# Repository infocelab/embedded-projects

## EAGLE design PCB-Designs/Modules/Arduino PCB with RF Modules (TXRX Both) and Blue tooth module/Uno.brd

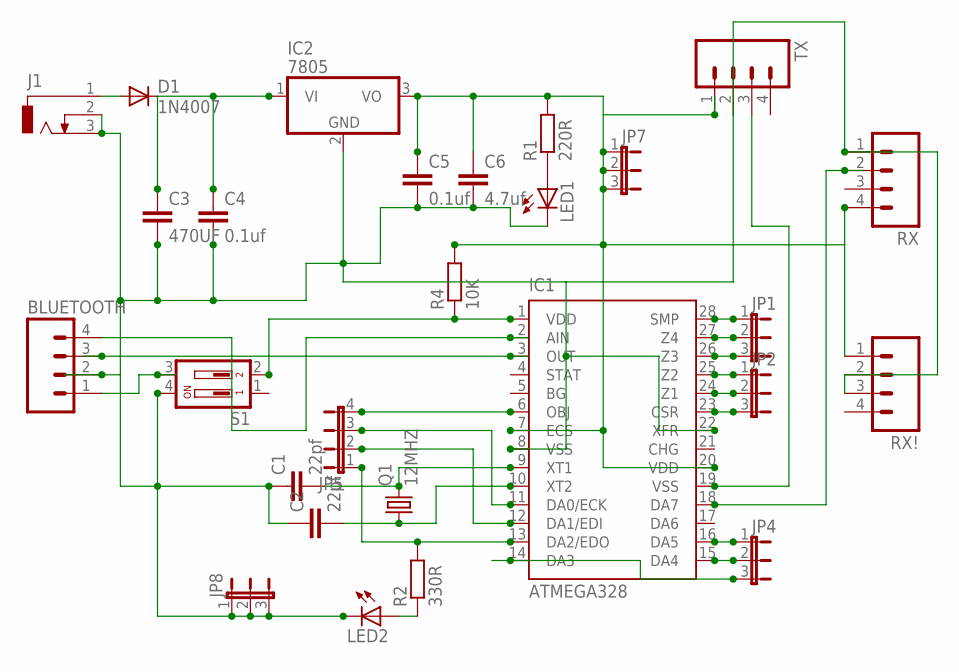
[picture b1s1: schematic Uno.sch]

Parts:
BLUETOOTH: M04; 04P
C1, C2: 22pf; C2.5-2
C3: 470UF; C2.5-2
C4, C5: 0.1uf; C2.5-2
C6: 4.7uf; C2.5-2
D1: 1N4007; DO41-10
IC1: ATMEGA328; DIL28-3
IC2: 7805; TO220V
J1: DCJ0303
JP1, JP2, JP4, JP7, JP8: JP2E; JP2
JP5: JP4E; JP4
LED1, LED2: LED3MM
Q1: 12MHZ; HC49/S
R1: 220R; 0207/10
R2: 330R; 0207/10
R4: 10K; 0207/10
RX: M04; 04P
RX!: M04; 04P
S1: DP02; DP-02
TX: M04; 04P

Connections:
unnamed: C1.2, IC1.9 (XT1), Q1.2
unnamed: C2.2, IC1.10 (XT2), Q1.1
unnamed: D1.A, J1.1
unnamed: C5.1, C6.1, IC1.7 (ECS), IC1.20 (VDD), IC2.3 (VO), JP7.1, JP7.2, JP7.3, R1.2, R4.2, RX.4, RX!.1, TX.1
unnamed: BLUETOOTH.2, C1.1, C2.1, C3.2, C4.2, C5.2, C6.2, IC1.8 (VSS), IC1.22 (XFR), IC2.2 (GND), J1.2, J1.3, JP8.1, JP8.2, JP8.3, LED1.K (C), LED2.K (C), RX.1, RX!.2, RX!.3, S1.4, TX.2
unnamed: LED1.A, R1.1
unnamed: C3.1, C4.1, D1.C, IC2.1 (VI)
unnamed: IC1.28 (SMP), JP1.1
unnamed: IC1.27 (Z4), JP1.2
unnamed: IC1.26 (Z3), JP1.3
unnamed: IC1.25 (Z2), JP2.1
unnamed: IC1.24 (Z1), JP2.2
unnamed: IC1.23 (CSR), JP2.3
unnamed: BLUETOOTH.4, IC1.2 (AIN)
unnamed: BLUETOOTH.1, S1.3
unnamed: BLUETOOTH.3, IC1.3 (OUT)
unnamed: IC1.6 (OBJ), JP5.4
unnamed: IC1.12 (DA1/EDI), JP5.2
unnamed: IC1.11 (DA0/ECK), JP5.3
unnamed: IC1.13 (DA2/EDO), JP5.1, R2.2
unnamed: IC1.14 (DA3), JP4.3
unnamed: IC1.15 (DA4), JP4.2
unnamed: IC1.16 (DA5), JP4.1
unnamed: IC1.18 (DA7), RX.2
unnamed: IC1.19 (VSS), TX.3
unnamed: IC1.1 (VDD), R4.1, S1.2
unnamed: LED2.A, R2.1

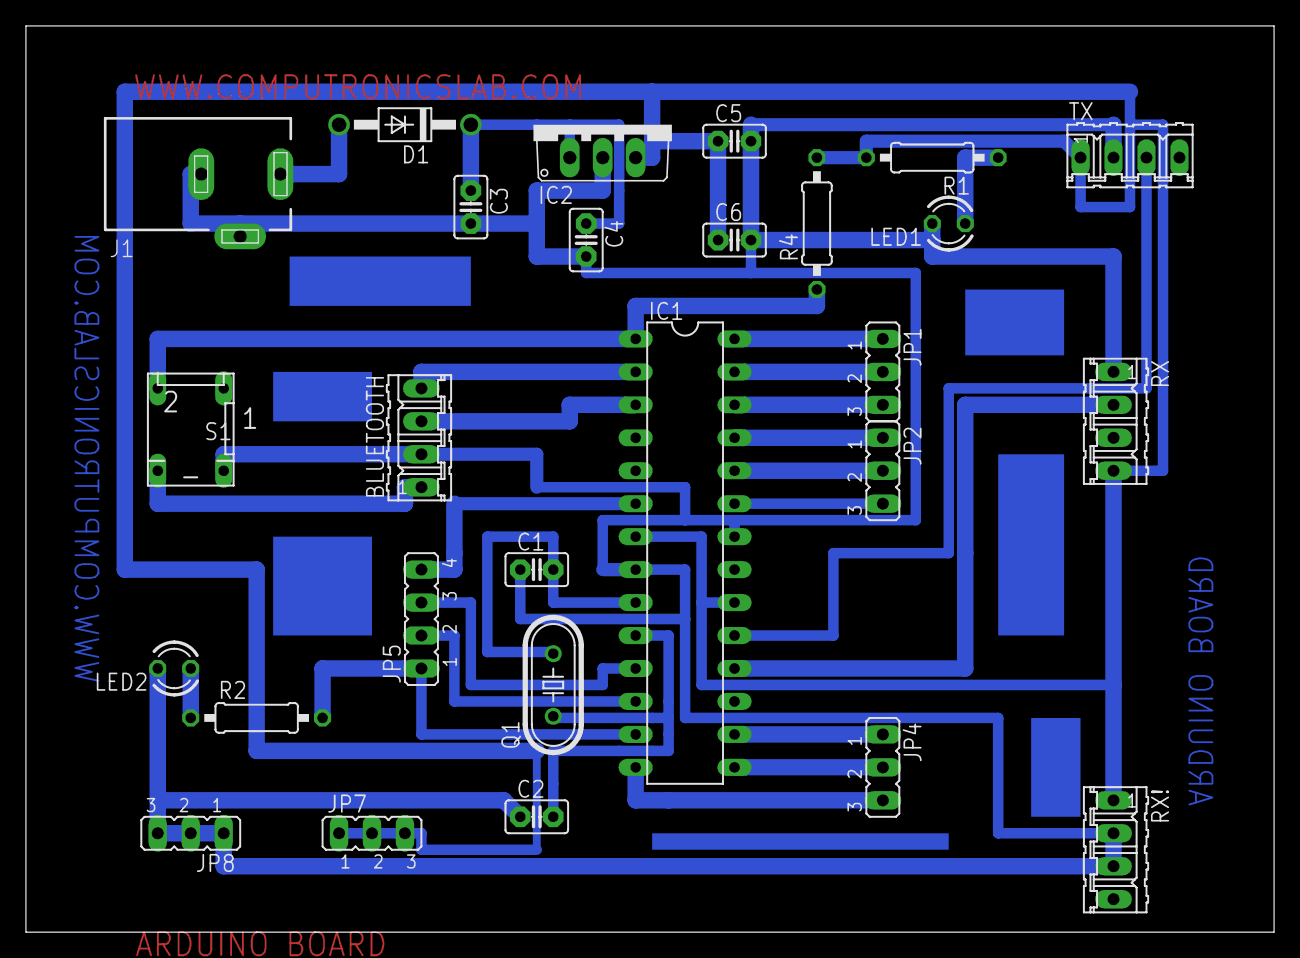
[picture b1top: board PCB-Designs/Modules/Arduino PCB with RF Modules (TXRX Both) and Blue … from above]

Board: 2 copper layers, 96.2 x 69.8 mm, 27 parts (0 on the bottom side), 27 nets.

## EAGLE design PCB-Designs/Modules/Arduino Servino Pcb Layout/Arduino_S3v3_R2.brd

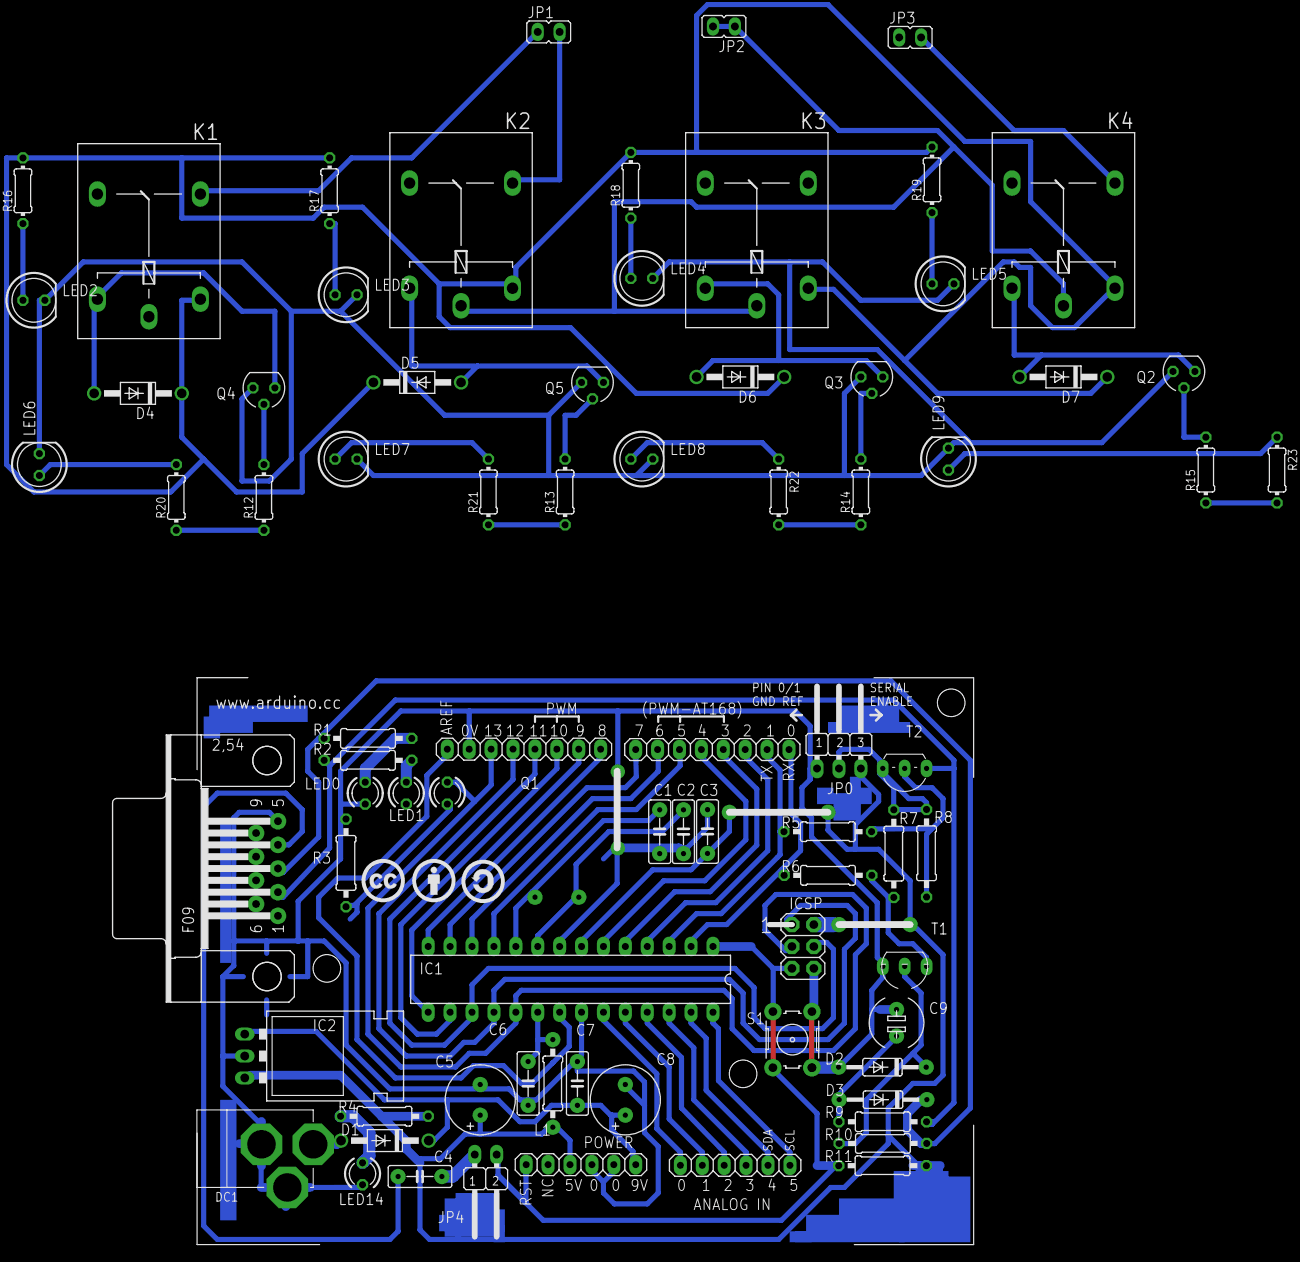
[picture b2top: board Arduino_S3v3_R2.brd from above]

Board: 2 copper layers, 81 parts (1 on the bottom side), 69 nets.

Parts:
C1, C2: 22p; C050-025X075
C3, C4, C6, C7: 100n; C050-025X075
C5, C8: 100u; E3,5-8
C9: 10u; E5-6
D1, D4, D5, D6, D7: 1N4004; DO41-10
D2, D3: 1N4148; DO35-10
DC1: DC21MMX; DC-21MM
IC1: ATMEGA8 (OR 168); DIL28-3
IC2: 78XXL
ICSP: ICSP; 2X03
J1: PORT D(D0-D7); 1X08
J2: PORT C(A0-A5); 1X06
J3: PORT B(D8-D13); 1X08
JP0: JP2W
JP1, JP2, JP3: JP1
JP4: AUTO RESET; JP1W
K1, K2, K3, K4: G5L; G5LE
L1: 100uH; 0207/10@1
LED0: RX; LED3MM
LED1: TX; LED3MM
LED2, LED3, LED4, LED5, LED6, LED7, LED8, LED9: LED5MM
LED13: L; LED3MM
LED14: POWER LED; LED3MM
POWER: 1X06
Q1: 16000; Q
Q2, Q3, Q4, Q5: BC547; SOT54A
R1, R2: 1K; 0207/10
R3, R4, R6: 1k; 0207/10
R5, R7, R8, R10, R11: 10k; 0207/10
R9: 4k7; 0207/10
R12, R13, R14, R15: 0204/7
R16, R17, R18, R19: 2.2K; 0204/7
R20, R21, R22, R23: 1K; 0204/7
S1: B3F-10XX
T1: BC547; TO92
T2: BC557; TO92-EBC
U$1: CC
U$2: BY
U$3: SA
X1: F09H

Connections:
+5V: C3.1, C5.+, IC1.7, IC2.OUT, ICSP.2, JP0.3, L1.2, POWER.3, R4.2, R11.2
+12V: D4.C, D5.C, D6.C, D7.C, K1.1, K2.1, K3.1, K4.1, R16.2, R17.2, R18.2, R19.2
AGND: LED2.K, LED3.K, LED4.K, LED5.K, LED6.K, LED7.K, LED8.K, LED9.K, Q2.E, Q3.E, Q4.E, Q5.E
AREF: IC1.21, J3.8
GND: C1.1, C2.1, C3.2, C5.-, C6.2, C7.1, C8.-, C9.+, D2.A, DC1.1, DC1.3, IC1.8, IC1.22, IC2.GND, ICSP.6, J3.7, JP0.1, LED0.K, LED1.K, LED14.K, POWER.4, POWER.5, R3.1, S1.1, S1.2, T1.1, X1.5
M8RXD: IC1.2, J1.1, R6.1
M8TXD: IC1.3, J1.2, R5.1
unnamed: IC1.18, ICSP.1, J3.5
unnamed: C9.-, D3.A, R9.1
unnamed: LED14.A, R4.1
unnamed: IC1.17, ICSP.4, J3.4
unnamed: IC1.14, J3.1
unnamed: C1.2, IC1.9, Q1.1
unnamed: C2.2, IC1.10, Q1.2
unnamed: D1.A, DC1.2
unnamed: JP2.1, JP2.2, K1.P, K2.P, K3.P, K4.P
unnamed: IC1.4, J1.3
unnamed: IC1.5, J1.4
unnamed: IC1.6, J1.5
unnamed: IC1.11, J1.6
unnamed: IC1.12, J1.7
unnamed: IC1.13, J1.8
unnamed: IC1.23, J2.1
unnamed: IC1.24, J2.2
unnamed: IC1.25, J2.3
unnamed: IC1.26, J2.4
unnamed: IC1.27, J2.5
unnamed: IC1.28, J2.6
unnamed: IC1.15, J3.2
unnamed: IC1.16, J3.3
unnamed: Q4.B, R12.2
unnamed: D3.C, R1.2, R10.2, X1.3
unnamed: R6.2, R7.1, T1.3
unnamed: R5.2, R8.2, T2.B
unnamed: Q5.B, R13.2
unnamed: D2.C, R10.1, T1.2
unnamed: Q3.B, R14.2
unnamed: LED13.K, R3.2
unnamed: LED1.A, R2.1
unnamed: LED0.A, R1.1
unnamed: C4.1, JP4.2
unnamed: Q2.B, R15.2
unnamed: D4.A, K1.2, Q4.C
unnamed: D5.A, K2.2, Q5.C
unnamed: C4.2, X1.4
unnamed: R2.2, R9.2, T2.C, X1.2
unnamed: D6.A, K3.2, Q3.C
unnamed: D7.A, K4.2, Q2.C
unnamed: C6.1, IC1.20, L1.1
unnamed: LED2.A, R16.1
unnamed: LED3.A, R17.1
unnamed: LED4.A, R18.1
unnamed: LED5.A, R19.1
unnamed: R12.1, R20.1
unnamed: R13.1, R21.1
unnamed: R14.1, R22.2
unnamed: LED6.A, R20.2
unnamed: LED7.A, R21.2
unnamed: LED8.A, R22.1
unnamed: LED9.A, R23.1
unnamed: JP1.1, K1.S
unnamed: JP1.2, K2.S
unnamed: JP3.1, K3.S
unnamed: JP3.2, K4.S
unnamed: R15.1, R23.2
RESET: IC1.1, ICSP.5, JP4.1, POWER.1, R11.1, S1.3, S1.4
SCK: IC1.19, ICSP.3, J3.6, LED13.A
SERIAL_VCC: JP0.2, R7.2, R8.1, T2.E
VIN: C7.2, C8.+, D1.C, IC2.IN, POWER.6

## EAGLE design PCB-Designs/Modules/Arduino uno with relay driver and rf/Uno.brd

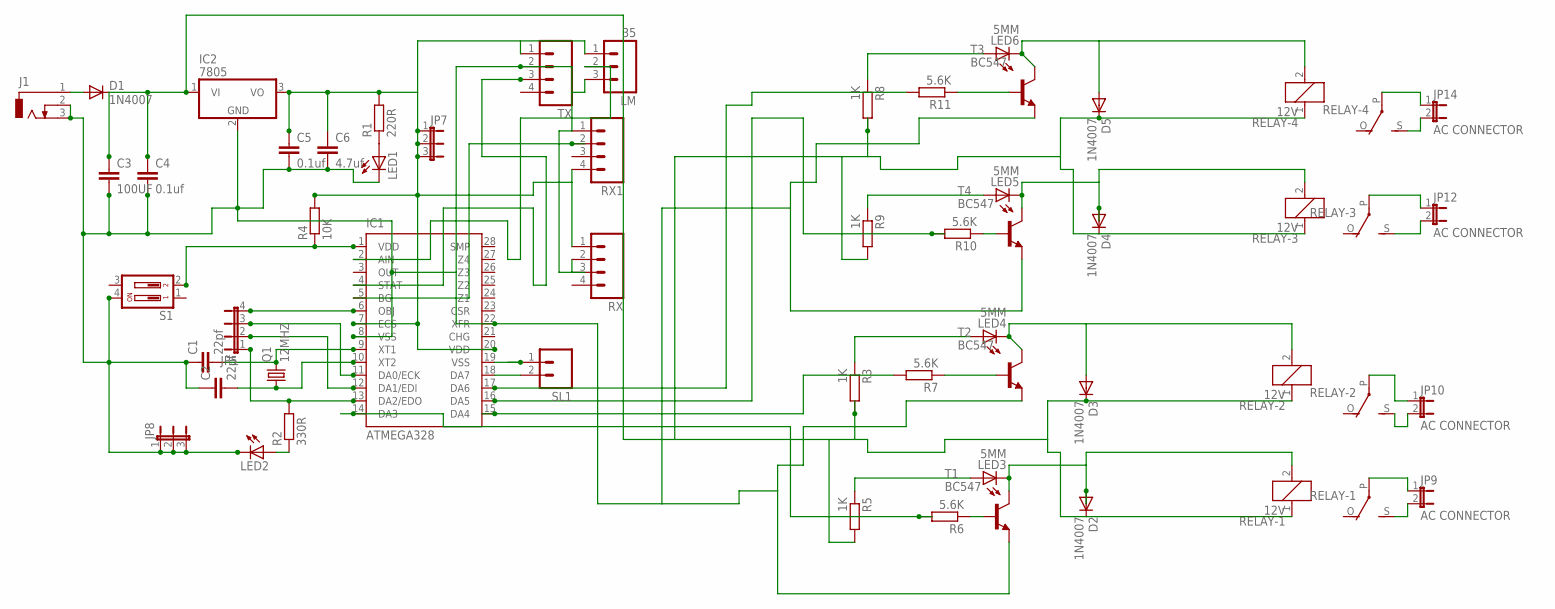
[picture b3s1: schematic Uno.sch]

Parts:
C1, C2: 22pf; C2.5-2
C3: 100UF; C2.5-2
C4, C5: 0.1uf; C2.5-2
C6: 4.7uf; C2.5-2
D1, D2, D3, D4, D5: 1N4007; DO41-10
IC1: ATMEGA328; DIL28-3
IC2: 7805; TO220V
J1: DCJ0303
JP5: JP4E; JP4
JP7, JP8: JP2E; JP2
JP9, JP10, JP12, JP14: AC CONNECTOR; JP1
LED1, LED2: LED3MM
LED3, LED4, LED5, LED6: 5MM; LED5MM
LM: 35; 03P
Q1: 12MHZ; HC49/S
R1: 220R; 0207/10
R2: 330R; 0207/10
R3, R5, R8, R9: 1K; 0204/7
R4: 10K; 0207/10
R6, R7, R10, R11: 5.6K; 0204/7
RELAY-1, RELAY-2, RELAY-3, RELAY-4: 12V; G5LE
RX, RX1: M04; 04P
S1: DP02; DP-02
SL1: M02; 02P
T1, T2, T3, T4: BC547; TO92
TX: M04; 04P

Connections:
unnamed: C1.2, IC1.9 (XT1), Q1.2
unnamed: C2.2, IC1.10 (XT2), Q1.1
unnamed: D1.A, J1.1
unnamed: C5.1, C6.1, IC1.7 (ECS), IC1.20 (VDD), IC2.3 (VO), JP7.1, JP7.2, JP7.3, LM.1, R1.2, R4.2, RX.1, RX1.4, TX.1
unnamed: IC1.18 (DA7), SL1.2
unnamed: LED1.A, R1.1
unnamed: C3.1, C4.1, D1.C, D2.C, D3.C, D4.C, D5.C, IC2.1 (VI), R3.2, R5.2, R8.2, R9.2, RELAY-1.1, RELAY-2.1, RELAY-3.1, RELAY-4.1
unnamed: IC1.2 (AIN), LM.2
unnamed: IC1.5 (BG), RX1.2
unnamed: IC1.4 (STAT), TX.3
unnamed: IC1.6 (OBJ), JP5.4
unnamed: IC1.12 (DA1/EDI), JP5.2
unnamed: IC1.11 (DA0/ECK), JP5.3
unnamed: IC1.13 (DA2/EDO), JP5.1, R2.2
unnamed: IC1.19 (VSS), SL1.1
unnamed: D2.A, LED3.K (C), RELAY-1.2, T1.3 (C)
unnamed: R7.1, T2.2 (B)
unnamed: R6.1, T1.2 (B)
unnamed: IC1.1 (VDD), R4.1, S1.2
unnamed: LED2.A, R2.1
unnamed: LED3.A, R5.1
unnamed: LED4.A, R3.1
unnamed: JP9.2, RELAY-1.S
unnamed: JP9.1, RELAY-1.P
unnamed: JP10.2, RELAY-2.S
unnamed: JP10.1, RELAY-2.P
unnamed: IC1.14 (DA3), R6.2
unnamed: D3.A, LED4.K (C), RELAY-2.2, T2.3 (C)
unnamed: D4.A, LED5.K (C), RELAY-3.2, T4.3 (C)
unnamed: R11.1, T3.2 (B)
unnamed: R10.1, T4.2 (B)
unnamed: LED5.A, R9.1
unnamed: LED6.A, R8.1
unnamed: JP12.2, RELAY-3.S
unnamed: JP12.1, RELAY-3.P
unnamed: JP14.2, RELAY-4.S
unnamed: JP14.1, RELAY-4.P
unnamed: C1.1, C2.1, C3.2, C4.2, C5.2, C6.2, IC1.8 (VSS), IC1.22 (XFR), IC2.2 (GND), J1.2, J1.3, JP8.1, JP8.2, JP8.3, LED1.K (C), LED2.K (C), LM.3, RX.2, RX1.1, S1.4, T1.1 (E), T2.1 (E), T3.1 (E), T4.1 (E), TX.2
unnamed: IC1.16 (DA5), R10.2
unnamed: IC1.17 (DA6), R11.2
unnamed: D5.A, LED6.K (C), RELAY-4.2, T3.3 (C)
unnamed: IC1.15 (DA4), R7.2

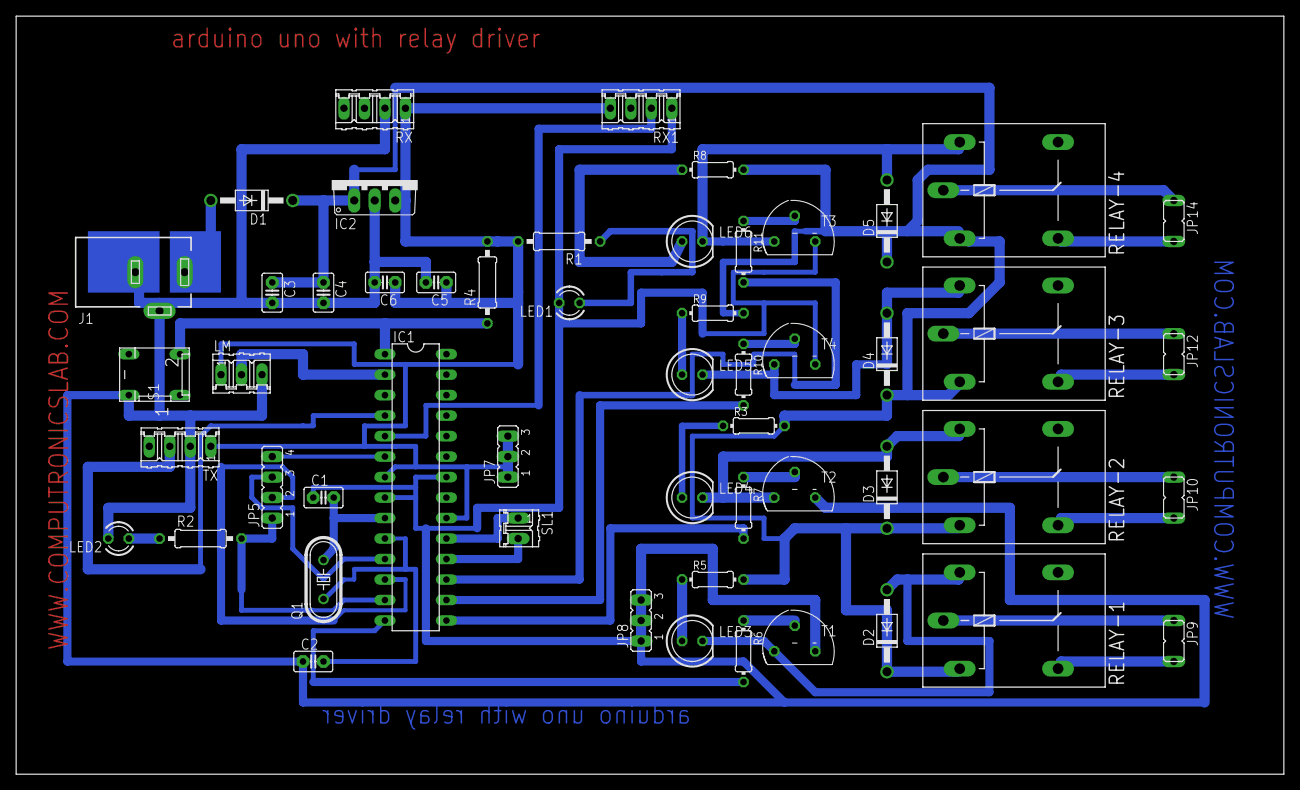
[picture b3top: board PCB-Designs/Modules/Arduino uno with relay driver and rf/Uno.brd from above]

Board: 2 copper layers, 157.2 x 94.0 mm, 53 parts (0 on the bottom side), 42 nets.

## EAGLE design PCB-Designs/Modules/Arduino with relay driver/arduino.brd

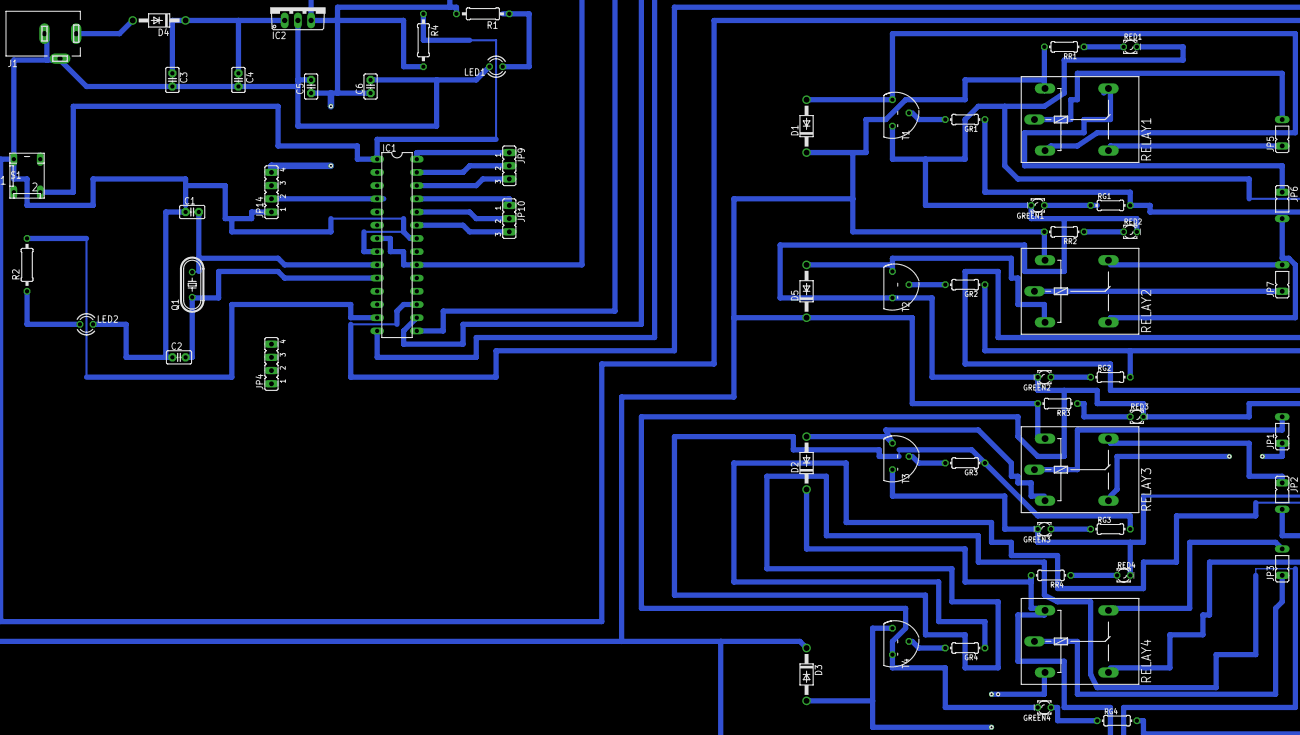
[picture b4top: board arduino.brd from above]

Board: 2 copper layers, 59 parts (0 on the bottom side), 48 nets.

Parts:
C1, C2: 22pf; C2.5-2
C3: 100UF; C2.5-2
C4, C5: 0.1uf; C2.5-2
C6: 4.7uf; C2.5-2
D1, D2, D3, D5: 1N4004; DO41-10
D4: 1N4007; DO41-10
GR1, GR2, GR3, GR4: 2.2k; 0204/7
GREEN1, GREEN2, GREEN3, GREEN4: LED_LD260
IC1: ATMEGA328; DIL28-3
IC2: 7805; TO220V
J1: DCJ0303
JP1, JP2, JP3, JP5, JP6, JP7: JP1
JP4, JP14: JP4
JP9, JP10: JP2
LED1, LED2: LED3MM
Q1: 12MHZ; HC49/S
R1: 220R; 0207/10
R2: 330R; 0207/10
R4: 10K; 0207/10
RED1, RED2, RED3, RED4: LED_LD260
RELAY1, RELAY2, RELAY3, RELAY4: G5L; G5LE
RG1, RG2, RG3, RG4: 1k; 0204/7
RR1, RR2, RR3, RR4: 2.2k; 0204/7
S1: DP-02
T1, T2, T3, T4: BC547; TO92

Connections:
unnamed: D1.A, RELAY1.1, T1.3
unnamed: RED1.A, RR1.1
unnamed: C1.2, IC1.9, Q1.2
unnamed: GR1.2, T1.2
unnamed: D5.A, RELAY2.1, T2.3
unnamed: JP5.1, RELAY1.S
unnamed: JP6.1, RELAY1.O
unnamed: JP5.2, RELAY1.P
unnamed: GREEN1.A, RG1.1
unnamed: D2.A, RELAY3.1, T3.3
unnamed: RED2.A, RR2.1
unnamed: C2.2, IC1.10, Q1.1
unnamed: GR2.2, T2.2
unnamed: JP6.2, RELAY2.S
unnamed: JP7.2, RELAY2.O
unnamed: JP7.1, RELAY2.P
unnamed: GREEN2.A, RG2.1
unnamed: C1.1, C2.1, C3.2, C4.2, C5.2, C6.2, GREEN1.K, GREEN2.K, GREEN3.K, GREEN4.K, IC1.8, IC1.22, IC2.2, J1.2, J1.3, JP14.1, LED1.K, LED2.K, RED1.K, RED2.K, RED3.K, RED4.K, S1.4, T1.1, T2.1, T3.1, T4.1
unnamed: RED3.A, RR3.1
unnamed: IC1.4, JP14.2
unnamed: GR3.2, T3.2
unnamed: JP2.1, RELAY3.O
unnamed: JP1.2, RELAY3.P
unnamed: GREEN3.A, RG3.1
unnamed: D3.A, T4.3
unnamed: RED4.A, RR4.1
unnamed: C3.1, C4.1, D4.C, IC2.1
unnamed: GR4.2, T4.2
unnamed: JP2.2, RELAY4.S
unnamed: JP3.2, RELAY4.O
unnamed: JP3.1, RELAY4.P
unnamed: GREEN4.A, RG4.1
unnamed: D4.A, J1.1
unnamed: C5.1, C6.1, D1.C, D2.C, D3.C, D5.C, IC1.7, IC1.20, IC2.3, R1.2, R4.2, RELAY1.2, RELAY2.2, RELAY3.2, RELAY4.2, RR1.2, RR2.2, RR3.2, RR4.2
unnamed: LED1.A, R1.1
unnamed: IC1.28, JP9.1
unnamed: IC1.27, JP9.2
unnamed: IC1.26, JP9.3
unnamed: IC1.25, JP10.1
unnamed: IC1.24, JP10.2
unnamed: IC1.23, JP10.3
unnamed: IC1.13, R2.2
unnamed: GR4.1, IC1.14, RG4.2
unnamed: GR3.1, IC1.15, RG3.2
unnamed: GR2.1, IC1.16, RG2.2
unnamed: GR1.1, IC1.17, RG1.2
unnamed: IC1.1, R4.1, S1.2
unnamed: LED2.A, R2.1

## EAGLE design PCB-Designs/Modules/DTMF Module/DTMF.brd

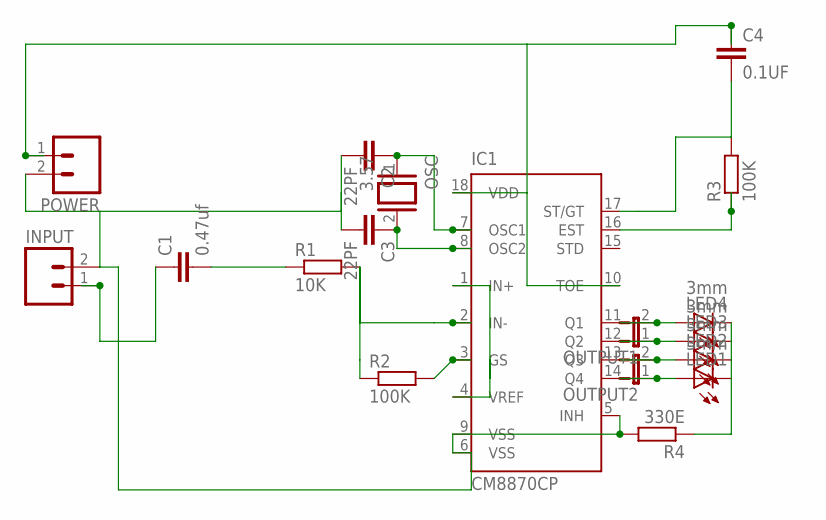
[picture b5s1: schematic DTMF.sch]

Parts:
C1: 0.47uf; C2.5-2
C2, C3: 22PF; C2.5-2
C4: 0.1UF; C2.5-2
IC1: CM8870CP; DIL18
INPUT: M02; 02P
LED1, LED2, LED3, LED4: 3mm; LED3MM
OSC: 3.57; QS
OUTPUT1, OUTPUT2: JP1E; JP1
POWER: M02; 02P
R1: 10K; 0204/7
R2, R3: 100K; 0204/7
R4: 330E; 0204/7

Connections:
unnamed: C2.2, C3.2, IC1.5 (INH), IC1.6 (VSS), IC1.9 (VSS), INPUT.2, POWER.2, R4.2
unnamed: C1.2, R1.1
unnamed: IC1.3 (GS), R2.2
unnamed: LED1.K (C), LED2.K (C), LED3.K (C), LED4.K (C), R4.1
unnamed: IC1.11 (Q1), LED4.A, OUTPUT1.2
unnamed: IC1.12 (Q2), LED3.A, OUTPUT1.1
unnamed: IC1.13 (Q3), LED2.A, OUTPUT2.2
unnamed: IC1.14 (Q4), LED1.A, OUTPUT2.1
unnamed: C4.1, IC1.10 (TOE), IC1.18 (VDD), POWER.1
unnamed: C1.1, INPUT.1
unnamed: IC1.2 (IN-), R1.2, R2.1
unnamed: IC1.1 (IN+), IC1.4 (VREF)
unnamed: C2.1, IC1.7 (OSC1), OSC.1
unnamed: C3.1, IC1.8 (OSC2), OSC.2
unnamed: IC1.16 (EST), R3.1
unnamed: C4.2, IC1.17 (ST/GT), R3.2

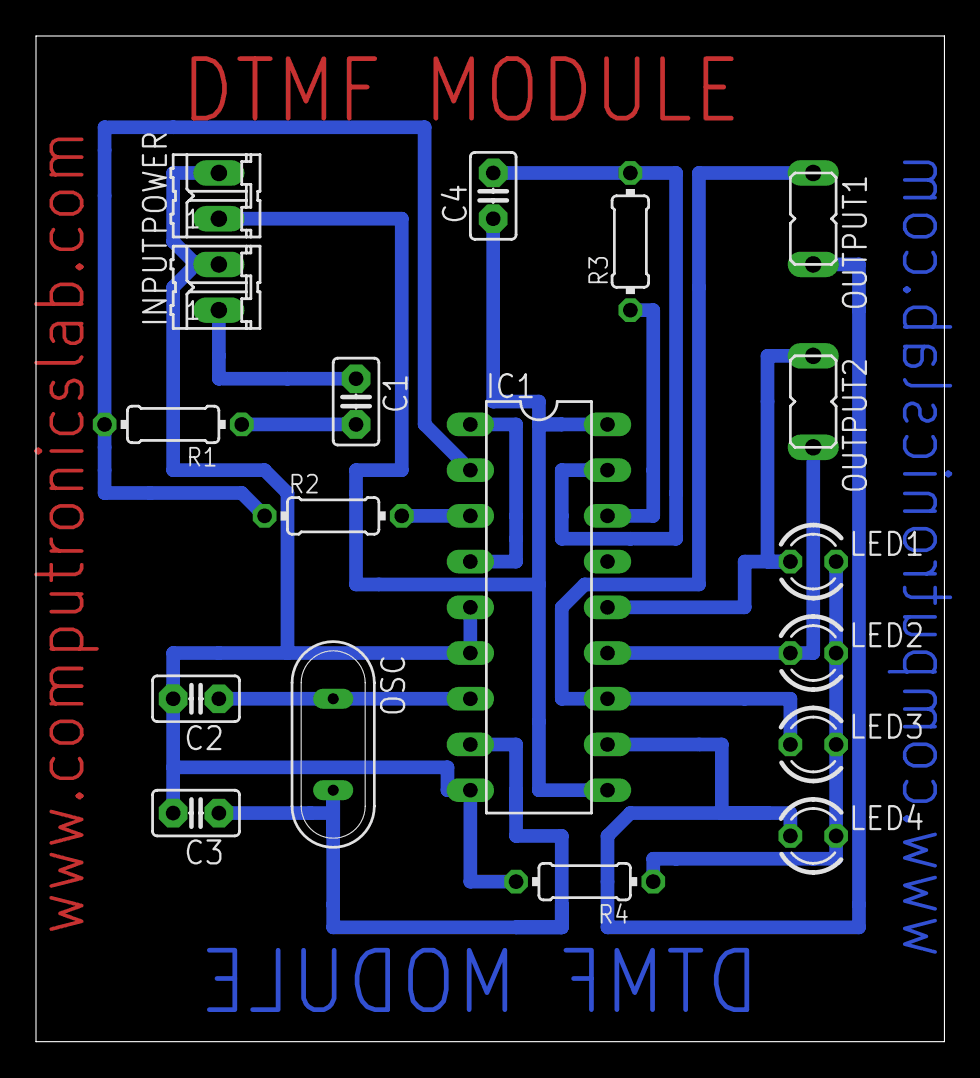
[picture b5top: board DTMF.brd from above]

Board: 2 copper layers, 50.5 x 55.9 mm, 18 parts (0 on the bottom side), 16 nets.

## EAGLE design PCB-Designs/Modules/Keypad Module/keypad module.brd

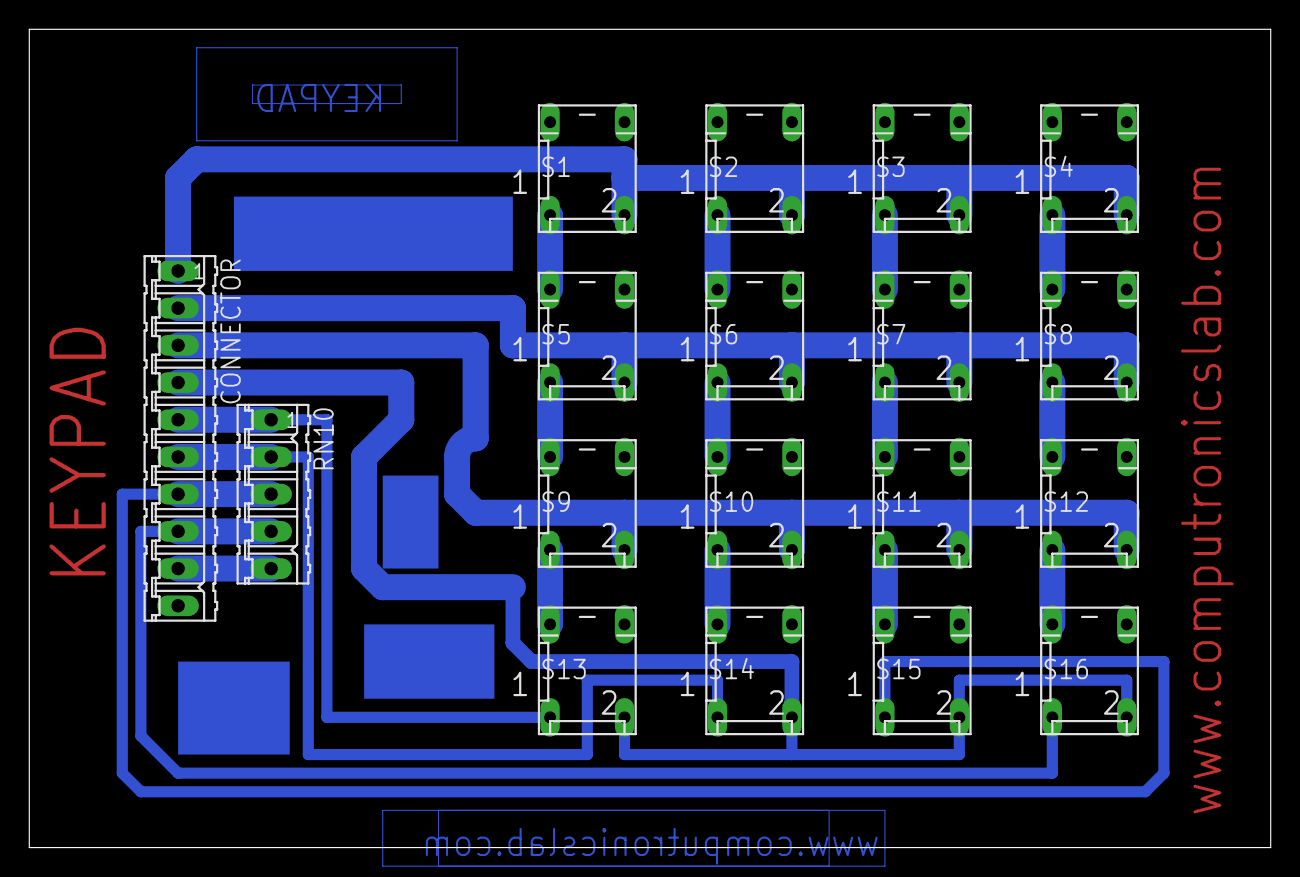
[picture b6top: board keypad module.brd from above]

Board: 2 copper layers, 84.8 x 55.9 mm, 18 parts (0 on the bottom side), 21 nets.

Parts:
CONNECTOR: 10pin; 10P
RN10: 5pin; 05P
S1, S2: push switch; DP-02
S3, S4, S5, S6, S7, S8, S9, S10, S11, S12, S13, S14, S15, S16: DP-02

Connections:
unnamed: CONNECTOR.1, S1.2, S2.2, S3.2, S4.2
unnamed: CONNECTOR.2, S5.2, S6.2, S7.2, S8.2
unnamed: CONNECTOR.3, S9.2, S10.2, S11.2, S12.2
unnamed: S7.1, S11.4
unnamed: S1.1, S5.4
unnamed: S5.1, S9.4
unnamed: S9.1, S13.4
unnamed: S2.1, S6.4
unnamed: S6.1, S10.4
unnamed: S10.1, S14.4
unnamed: S3.1, S7.4
unnamed: S4.1, S8.4
unnamed: S11.1, S15.4
unnamed: S12.1, S16.4
unnamed: S8.1, S12.4
unnamed: CONNECTOR.4, S13.2, S14.2, S15.2, S16.2
unnamed: CONNECTOR.5, RN10.1, S13.1
unnamed: CONNECTOR.6, RN10.2, S14.1
unnamed: CONNECTOR.7, RN10.3, S15.1
unnamed: CONNECTOR.8, RN10.4, S16.1
unnamed: CONNECTOR.9, RN10.5

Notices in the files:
PCB-Designs/Modules/Arduino Servino Pcb Layout/Arduino_S3v3_R2.brd:
Released under the Creative Commons Attribution Share-Alike 2.5 License
http://creativecommons.org/licenses/by-sa/2.5
CC BY SA 2.5
